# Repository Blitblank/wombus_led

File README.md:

# WombusLED

Firmware for controlling WS2812b matrices with ESP-IDF.
This embedded application is designed around the hardware described in this repository, though the goal is to broaden to other hardware targets.
The primary target is the ESP32-S3 Wroom1 N4R2 module.
KiCad schematic and PCB layout files can be found in the pcb directory.

Scripts are in scripts directory, named appropriately.

## Development plan: 
- [x] Create repository.
- [x] Build setup, get working hello-world program.
- [x] Develop 7-segment display driver for the soburg-v2 board, which uses 32-bit shift registers.
    Ensures functional hardware interaction and interface design.
- [x] Develop WS2812b driver, would be nice to have some kind of testing for this.
- [x] Develop WS2812b interface. I like the FastLed library for Arduino so might have a lot of similar functionality.
- [ ] Implement proper app structure, with error checking and performance profiling
- [ ] Add a couple LED effects- the random blink and rainbow sweep are easy ones.
- [ ] Create a mock LED panel that executes natively to test LED effects outside of hardware. (SDL2 or something)
      Should use the same interface but a different driver (that's probably integrated into the program)
      Needs to be updated to support the same control interfaces implemented on hardware.
- [ ] Add support for the aforementioned hardware control interfaces.
      (Dedicated control board may vary, main one not even designed yet)
      Buttons for switching effects, potentiometers, rotary encoders, 7 segement displays, OLED panel, etc.
- [ ] Checkpoint at a Conway's Game of Life effect that can be modified by controls (speed, brightness, reset)
- [ ] Design this far out is murky, anything past this point is a future ambition
- [ ] MicroSD card for bitmap effects. Implies custom images and animations, config for which can be in a yaml or something
- [ ] Microphone for sound-based effects like a spectrum analyzer
    
This is basic but hopefully can be good platform for future WS2812b projects.

## Scripts:
After cloning: $ ./scripts/repo-setup # installs esp-idf, sets up target configurations\
To build:      $ ./scripts/build.sh\
To flash:      $ ./scripts/flash.sh # note: flash.sh automatically builds\
To monitor:    $ ./scripts/monitor.sh\

## TODOs for developers
- [ ] Move all hardware specifications to config/Kconfig.projbuild file. (things like NUM_LEDS, pins.h, ssd_digits, etc.)
- [ ] Create an effect base class for effects to inherit from
- [ ] Attach interrupts for hardware inputs
- [ ] Human I/O (like from buttons, knobs) needs to be in its own io task. Other tasks will be injected with a general I/O interface
- [ ] Investigate putting the wsled task on a separate core from io and such
- [ ] Wsled interface needs a platform for matrix creation

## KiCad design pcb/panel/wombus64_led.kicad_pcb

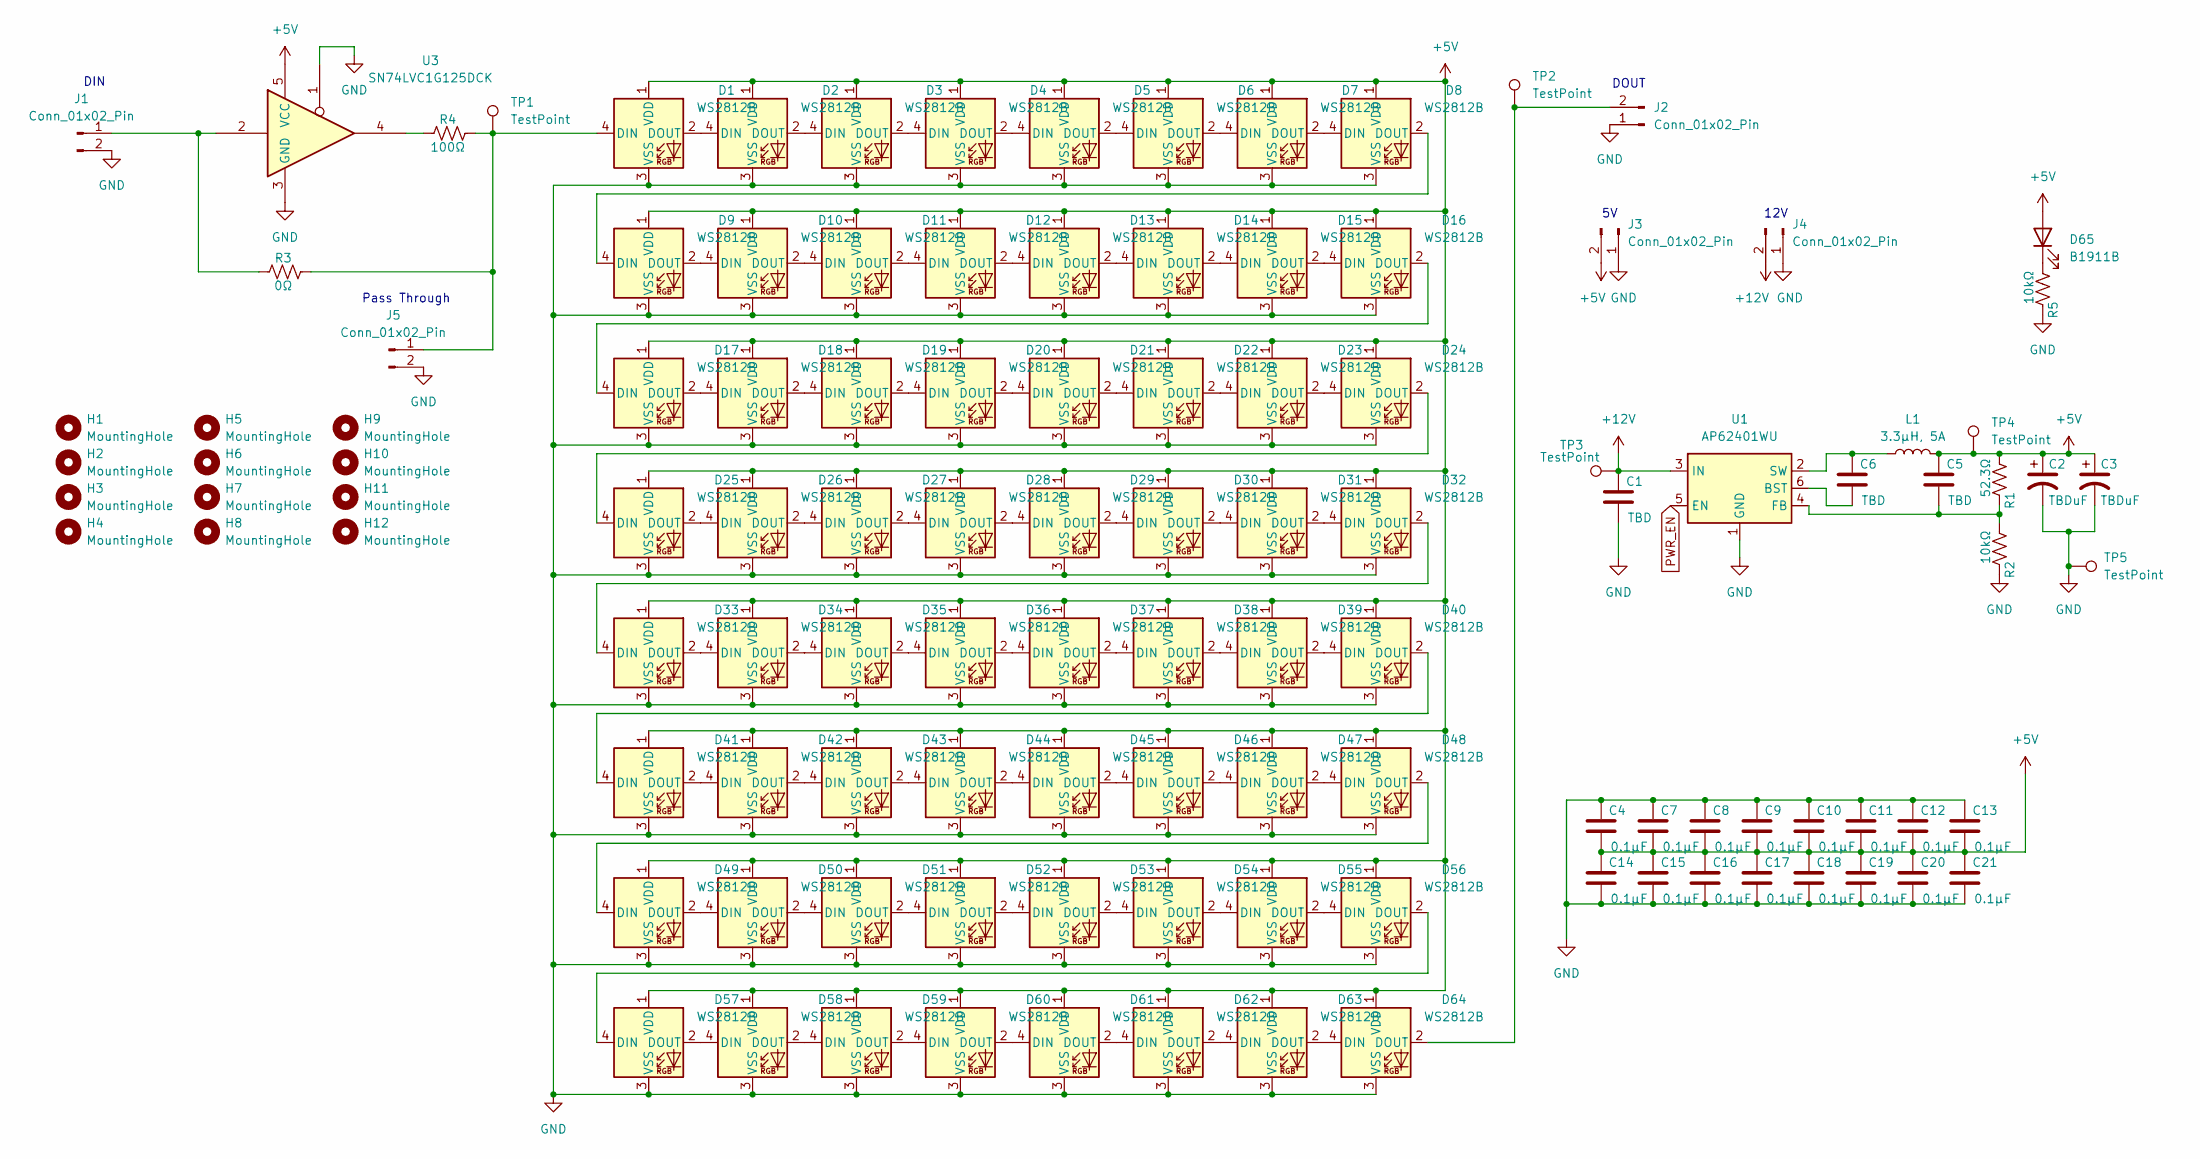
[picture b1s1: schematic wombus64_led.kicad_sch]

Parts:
C1, C5, C6: TBD; C_0603_1608Metric
C2, C3: TBDuF; CP_Radial_D8.0mm_P5.00mm
C4, C7, C8, C9, C10, C11, C12, C13, C14, C15, C16, C17, C18, C19, C20, C21: 0.1μF; C_0603_1608Metric
D1, D2, D3, D4, D5, D6, D7, D8, D9, D10, D11, D12, D13, D14, D15, D16, D17, D18, D19, D20, D21, D22, D23, D24, D25, D26, D27, D28, D29, D30, D31, D32, D33, D34, D35, D36, D37, D38, D39, D40, D41, D42, D43, D44, D45, D46, D47, D48, D49, D50, D51, D52, D53, D54, D55, D56, D57, D58, D59, D60, D61, D62, D63, D64: WS2812B; LED_WS2812B_PLCC4_5.0x5.0mm_P3.2mm
D65: B1911B; D_0603_1608Metric
H1, H2, H3, H4, H5, H6, H7, H8, H9, H10, H11, H12: MountingHole; MountingHole_3.2mm_M3_Pad
J1, J2, J3, J4, J5: Conn_01x02_Pin; JST_PH_S2B-PH-K_1x02_P2.00mm_Horizontal
L1: 3.3μH, 5A; L_TDK_VLS6045EX_VLS6045AF
R1: 52.3Ω; R_0603_1608Metric
R2, R5: 10kΩ; R_0603_1608Metric
R3: 0Ω; R_0603_1608Metric
R4: 100Ω; R_0603_1608Metric
TP1, TP2, TP3, TP4, TP5: TestPoint; TestPoint_Pad_D1.0mm
U1: AP62401WU; TSOT-23-6
U3: SN74LVC1G125DCK; Texas_R-PDSO-G5_DCK-5

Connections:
+5V: C2.1, C3.1, C4.2, C5.1, C7.2, C8.2, C9.2, C10.2, C11.2, C12.2, C13.2, C14.1, C15.1, C16.1, C17.1, C18.1, C19.1, C20.1, C21.1, D1.1 (VDD), D2.1 (VDD), D3.1 (VDD), D4.1 (VDD), D5.1 (VDD), D6.1 (VDD), D7.1 (VDD), D8.1 (VDD), D9.1 (VDD), D10.1 (VDD), D11.1 (VDD), D12.1 (VDD), D13.1 (VDD), D14.1 (VDD), D15.1 (VDD), D16.1 (VDD), D17.1 (VDD), D18.1 (VDD), D19.1 (VDD), D20.1 (VDD), D21.1 (VDD), D22.1 (VDD), D23.1 (VDD), D24.1 (VDD), D25.1 (VDD), D26.1 (VDD), D27.1 (VDD), D28.1 (VDD), D29.1 (VDD), D30.1 (VDD), D31.1 (VDD), D32.1 (VDD), D33.1 (VDD), D34.1 (VDD), D35.1 (VDD), D36.1 (VDD), D37.1 (VDD), D38.1 (VDD), D39.1 (VDD), D40.1 (VDD), D41.1 (VDD), D42.1 (VDD), D43.1 (VDD), D44.1 (VDD), D45.1 (VDD), D46.1 (VDD), D47.1 (VDD), D48.1 (VDD), D49.1 (VDD), D50.1 (VDD), D51.1 (VDD), D52.1 (VDD), D53.1 (VDD), D54.1 (VDD), D55.1 (VDD), D56.1 (VDD), D57.1 (VDD), D58.1 (VDD), D59.1 (VDD), D60.1 (VDD), D61.1 (VDD), D62.1 (VDD), D63.1 (VDD), D64.1 (VDD), D65.2 (A), J3.2, L1.2, R1.1, TP4.1, U3.5 (VCC)
+12V: C1.1, J4.2, TP3.1, U1.3 (IN)
GND: C1.2, C2.2, C3.2, C4.1, C7.1, C8.1, C9.1, C10.1, C11.1, C12.1, C13.1, C14.2, C15.2, C16.2, C17.2, C18.2, C19.2, C20.2, C21.2, D1.3 (VSS), D2.3 (VSS), D3.3 (VSS), D4.3 (VSS), D5.3 (VSS), D6.3 (VSS), D7.3 (VSS), D8.3 (VSS), D9.3 (VSS), D10.3 (VSS), D11.3 (VSS), D12.3 (VSS), D13.3 (VSS), D14.3 (VSS), D15.3 (VSS), D16.3 (VSS), D17.3 (VSS), D18.3 (VSS), D19.3 (VSS), D20.3 (VSS), D21.3 (VSS), D22.3 (VSS), D23.3 (VSS), D24.3 (VSS), D25.3 (VSS), D26.3 (VSS), D27.3 (VSS), D28.3 (VSS), D29.3 (VSS), D30.3 (VSS), D31.3 (VSS), D32.3 (VSS), D33.3 (VSS), D34.3 (VSS), D35.3 (VSS), D36.3 (VSS), D37.3 (VSS), D38.3 (VSS), D39.3 (VSS), D40.3 (VSS), D41.3 (VSS), D42.3 (VSS), D43.3 (VSS), D44.3 (VSS), D45.3 (VSS), D46.3 (VSS), D47.3 (VSS), D48.3 (VSS), D49.3 (VSS), D50.3 (VSS), D51.3 (VSS), D52.3 (VSS), D53.3 (VSS), D54.3 (VSS), D55.3 (VSS), D56.3 (VSS), D57.3 (VSS), D58.3 (VSS), D59.3 (VSS), D60.3 (VSS), D61.3 (VSS), D62.3 (VSS), D63.3 (VSS), D64.3 (VSS), J1.2, J2.1, J3.1, J4.1, J5.2, R2.2, R5.2, TP5.1, U1.1 (GND), U3.1, U3.3 (GND)
unnamed: D1.4 (DIN), J5.1, R3.2, R4.2, TP1.1
unnamed: D1.2 (DOUT), D2.4 (DIN)
unnamed: D2.2 (DOUT), D3.4 (DIN)
unnamed: D3.2 (DOUT), D4.4 (DIN)
unnamed: D4.2 (DOUT), D5.4 (DIN)
unnamed: D5.2 (DOUT), D6.4 (DIN)
unnamed: D6.2 (DOUT), D7.4 (DIN)
unnamed: D7.2 (DOUT), D8.4 (DIN)
unnamed: D8.2 (DOUT), D9.4 (DIN)
unnamed: D9.2 (DOUT), D10.4 (DIN)
unnamed: D10.2 (DOUT), D11.4 (DIN)
unnamed: D11.2 (DOUT), D12.4 (DIN)
unnamed: D12.2 (DOUT), D13.4 (DIN)
unnamed: D13.2 (DOUT), D14.4 (DIN)
unnamed: D14.2 (DOUT), D15.4 (DIN)
unnamed: D15.2 (DOUT), D16.4 (DIN)
unnamed: D16.2 (DOUT), D17.4 (DIN)
unnamed: D17.2 (DOUT), D18.4 (DIN)
unnamed: D18.2 (DOUT), D19.4 (DIN)
unnamed: D19.2 (DOUT), D20.4 (DIN)
unnamed: D20.2 (DOUT), D21.4 (DIN)
unnamed: D21.2 (DOUT), D22.4 (DIN)
unnamed: D22.2 (DOUT), D23.4 (DIN)
unnamed: D23.2 (DOUT), D24.4 (DIN)
unnamed: D24.2 (DOUT), D25.4 (DIN)
unnamed: D25.2 (DOUT), D26.4 (DIN)
unnamed: D26.2 (DOUT), D27.4 (DIN)
unnamed: D27.2 (DOUT), D28.4 (DIN)
unnamed: D28.2 (DOUT), D29.4 (DIN)
unnamed: D29.2 (DOUT), D30.4 (DIN)
unnamed: D30.2 (DOUT), D31.4 (DIN)
unnamed: D31.2 (DOUT), D32.4 (DIN)
unnamed: D32.2 (DOUT), D33.4 (DIN)
unnamed: D33.2 (DOUT), D34.4 (DIN)
unnamed: D34.2 (DOUT), D35.4 (DIN)
unnamed: D35.2 (DOUT), D36.4 (DIN)
unnamed: D36.2 (DOUT), D37.4 (DIN)
unnamed: D37.2 (DOUT), D38.4 (DIN)
unnamed: D38.2 (DOUT), D39.4 (DIN)
unnamed: D39.2 (DOUT), D40.4 (DIN)
unnamed: D40.2 (DOUT), D41.4 (DIN)
unnamed: D41.2 (DOUT), D42.4 (DIN)
unnamed: D42.2 (DOUT), D43.4 (DIN)
unnamed: D43.2 (DOUT), D44.4 (DIN)
unnamed: D44.2 (DOUT), D45.4 (DIN)
unnamed: D45.2 (DOUT), D46.4 (DIN)
unnamed: D46.2 (DOUT), D47.4 (DIN)
unnamed: D47.2 (DOUT), D48.4 (DIN)
unnamed: D48.2 (DOUT), D49.4 (DIN)
unnamed: D49.2 (DOUT), D50.4 (DIN)
unnamed: D50.2 (DOUT), D51.4 (DIN)
unnamed: D51.2 (DOUT), D52.4 (DIN)
unnamed: D52.2 (DOUT), D53.4 (DIN)
unnamed: D53.2 (DOUT), D54.4 (DIN)
unnamed: D54.2 (DOUT), D55.4 (DIN)
unnamed: D55.2 (DOUT), D56.4 (DIN)
unnamed: D56.2 (DOUT), D57.4 (DIN)
unnamed: D57.2 (DOUT), D58.4 (DIN)
unnamed: D58.2 (DOUT), D59.4 (DIN)
unnamed: D59.2 (DOUT), D60.4 (DIN)
unnamed: D60.2 (DOUT), D61.4 (DIN)
unnamed: D61.2 (DOUT), D62.4 (DIN)
unnamed: D62.2 (DOUT), D63.4 (DIN)
unnamed: D63.2 (DOUT), D64.4 (DIN)
unnamed: D64.2 (DOUT), J2.2, TP2.1
unnamed: D65.1 (K), R5.1
unnamed: J1.1, R3.1, U3.2
unnamed: R4.1, U3.4
unnamed: C6.2, U1.6 (BST)
unnamed: C5.2, R1.2, R2.1, U1.4 (FB)
unnamed: C6.1, L1.1, U1.2 (SW)
PWR_EN: U1.5 (EN)

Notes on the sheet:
Pass Through
12V
DIN
DOUT

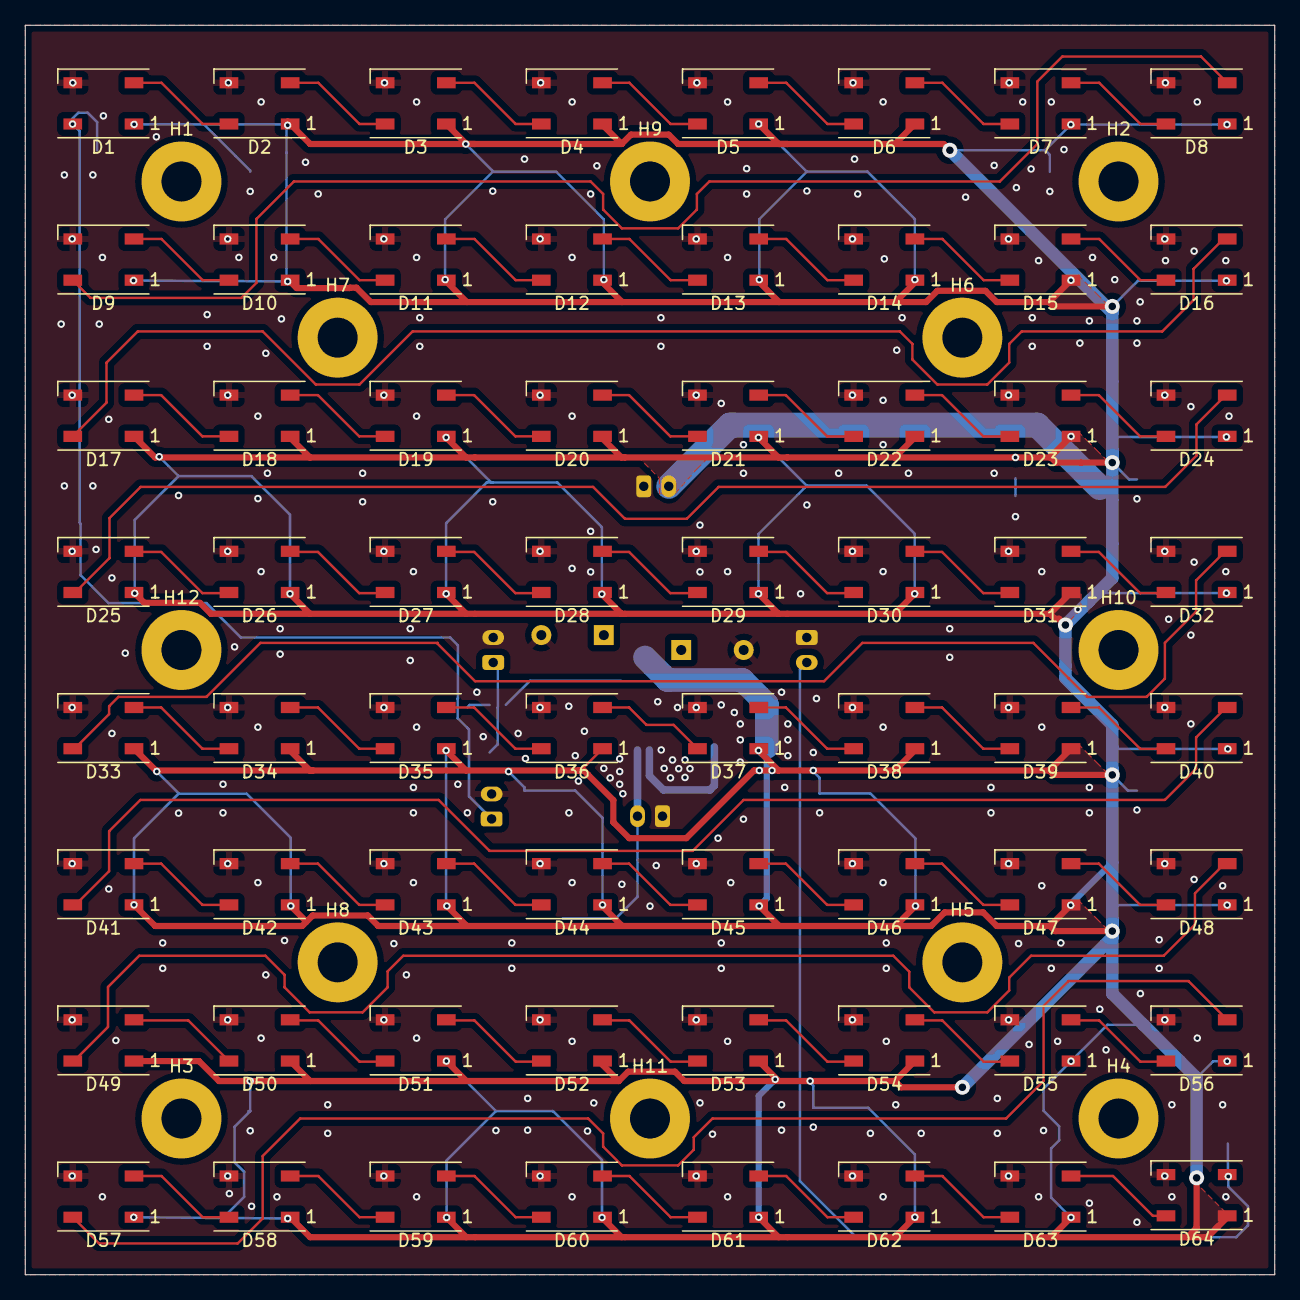
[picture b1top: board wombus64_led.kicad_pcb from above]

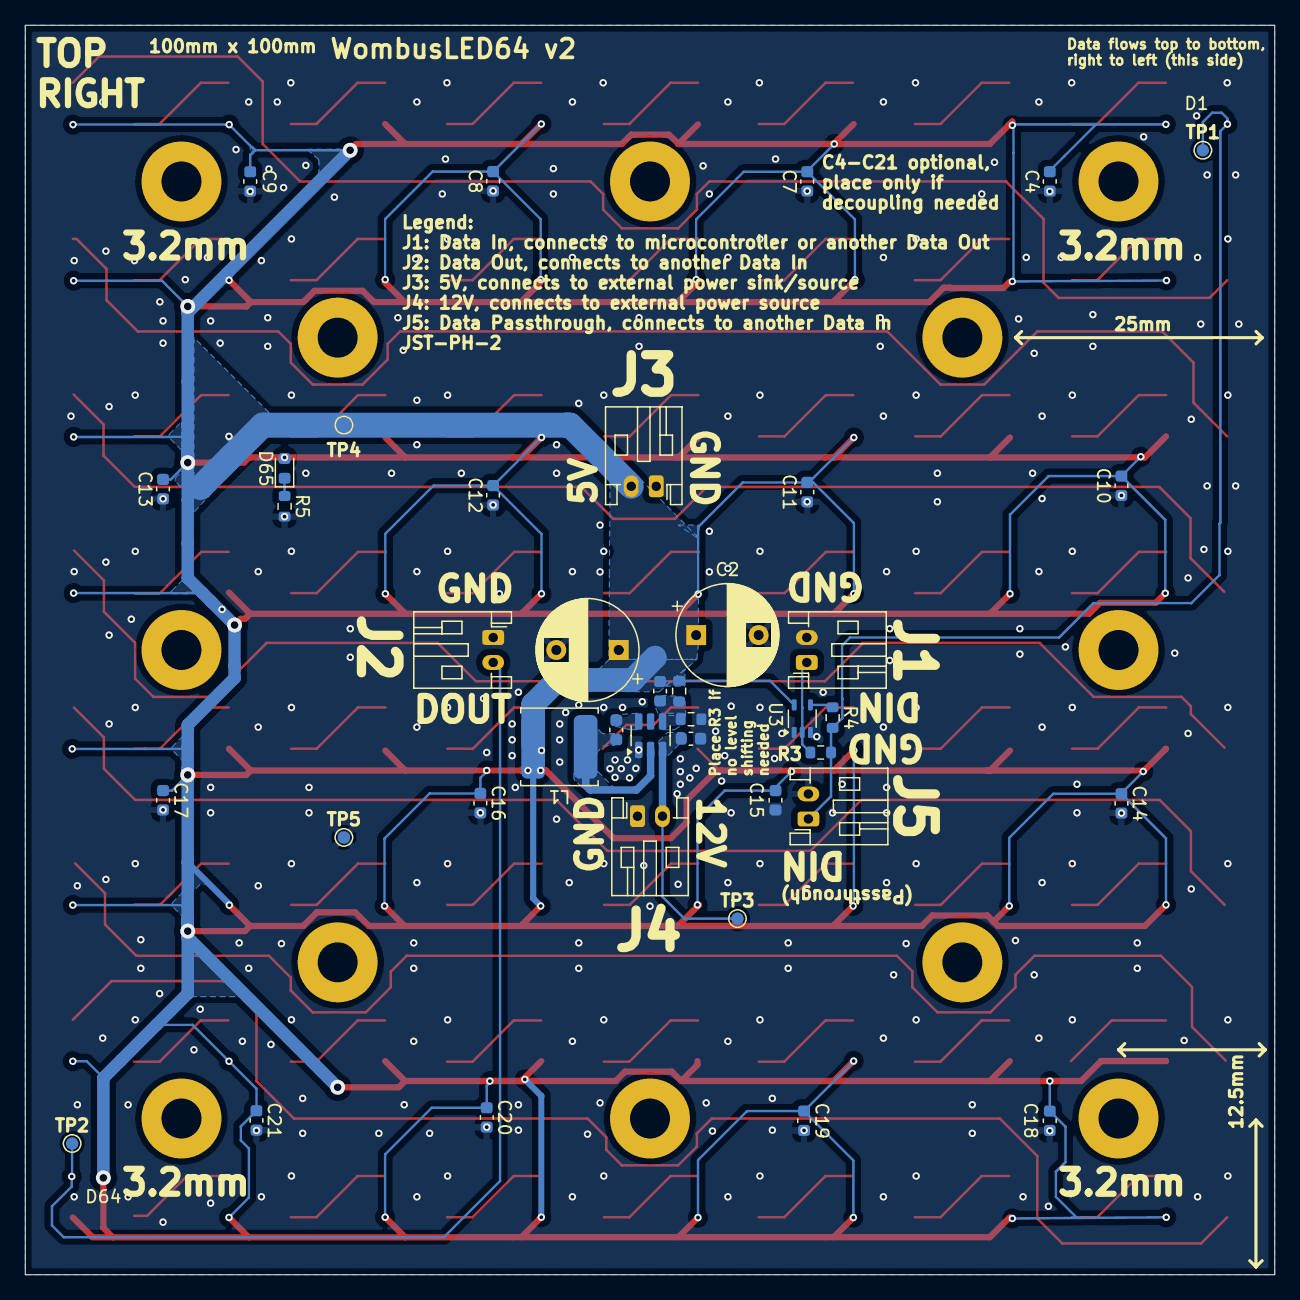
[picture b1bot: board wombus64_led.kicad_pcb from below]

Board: 2 copper layers, 100.0 x 100.0 mm, 116 parts (40 on the bottom side), 74 nets.

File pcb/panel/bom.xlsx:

| Category | Part Name | Schematic Reference | Supplier | Part # | Datasheet | Unit Price | Quantity | Shipping | Total Price | Notes |  | # Per Unit | Partial Cost |  | Notes
 | Addressable LED | WS2812B | D1-D64 | Aliexpress | - | link | 2.5000000000000001E-2 | 1000 | 0 | 25 |  |  | 64 | 1.6
 | Buck Converter | AP62401WU | U1 | Digikey | 31-AP62401WU-7CT-ND | link | 0.22789999999999999 | 100 | 0 | 22.79 |  |  | 1 | 0.22789999999999999
 | Inductor | 3.3μH, 5A | L1 | Digikey | 445-173052-1-ND | link | 0.23330000000000001 | 100 | 0 | 23.330000000000002 |  |  | 1 | 0.23330000000000001
 | WTB Connector | JST PH-2 Horizontal | J1-J5 | Digikey | 455-1719-ND | link | 6.9800000000000001E-2 | 100 | 0 | 6.98 |  |  | 5 | 0.34899999999999998
 | Level Shifter | SN74LVC1G125DCK | U3 | Digikey | 296-11604-1-ND | link | 0.06 | 50 | 0 | 3 |  |  | 0 | 0
 | Indicator LED (Red) | B1911R | D65 | Digikey | LED RED DIFFUSED 0603 SMD | link | 4.2999999999999997E-2 | 50 | 0 | 2.15 |  |  | 1 | 4.2999999999999997E-2
 |  |  |  |  |  |  |  |  | 0 | 0 |  |  |  | 0
 | Resistor | 52.3kΩ 1%, 0603 | R1 | Digikey | 311-52.3KHRCT-ND | link | 1.06E-2 | 100 | 0 | 1.06 |  |  | 1 | 1.06E-2
 | Resistor | 10kΩ 1%, 0603 | R2, R5 | Digikey | already have lots |  | 0.01 | 0 | 0 | 0 |  |  | 2 | 0.02
 | Resistor | 0Ω, 0603 | R3 | Digikey | already have lots |  | 0.01 | 0 | 0 | 0 |  |  | 1 | 0.01
 | Resistor | 100Ω 1%, 0603 | R4 | Digikey | CR0603-FX-1000ELFCT-ND | link | 9.1000000000000004E-3 | 100 | 0 | 0.91 |  |  | 1 | 9.1000000000000004E-3
 |  |  |  |  |  |  |  |  | 0 | 0 |  |  |  | 0
 | Capacitor, Ceramic | 10μF 6.3V, 0603 | C1 | Digikey | already have lots |  | 8.0000000000000002E-3 | 0 | 0 | 0 |  |  | 1 | 8.0000000000000002E-3
 | Capacitor, Electrolytic | 100μF 25V | C2, C3 | Aliexpress | - |  | 2.7400000000000001E-2 | 50 | 0 | 1.37 |  |  | 2 | 5.4800000000000001E-2
 | Capacitor, Ceramic | 0.1μF 25V, 0603 | C4, C6-C21 | Digikey | already have lots |  | 8.0000000000000002E-3 | 0 | 0 | 0 |  |  | 1 | 8.0000000000000002E-3
 | Capacitor, Ceramic | 20pF 50pF, 0603 | C5 | Digikey | already have lots |  | 8.0000000000000002E-3 | 0 | 0 | 0 |  |  | 1 | 8.0000000000000002E-3
 |  |  |  |  |  |  |  |  | 0 | 0 |  |  |  | 0
 |  |  |  |  |  |  |  |  | 0 | 0 |  |  |  | 0
 |  |  |  |  |  |  |  |  | 0 | 0 |  |  |  | 0
 |  |  |  |  |  |  |  |  | 0 | 0 |  |  |  | 0
 |  |  |  |  |  |  |  |  | 0 | 0 |  |  |  | 0
 |  |  |  |  |  |  |  |  | 0 | 0 |  |  |  | 0
 |  |  |  |  |  |  |  |  | 0 | 0 |  |  |  | 0
 |  |  |  |  |  |  |  |  | 0 | 0 |  |  |  | 0
 |  |  |  |  |  |  |  |  | 0 | 0 |  |  |  | 0
 |  |  |  |  |  |  |  |  | 0 | 0 |  |  |  | 0
 |  |  |  |  |  |  |  |  | 0 | 0 |  |  |  | 0
 |  |  |  |  |  |  |  |  | 0 | 0 |  |  |  | 0
 |  |  |  |  |  |  |  |  | 0 | 0 |  |  |  | 0
 |  |  |  |  |  |  |  |  | 0 | 0 |  |  |  | 0
 |  |  |  |  |  |  |  |  | 0 | 0 |  |  |  | 0
 |  |  |  |  |  |  |  |  | 0 | 0 |  |  |  | 0
 |  |  |  |  |  |  |  |  | 0 | 0 |  |  |  | 0
 |  |  |  |  |  |  |  |  | 0 | 0 |  |  |  | 0
 |  |  |  |  |  |  |  |  | 0 | 0 |  |  |  | 0
 |  |  |  |  |  |  |  |  | 0 | 0 |  |  |  | 0
 |  |  |  |  |  |  |  |  | 0 | 0 |  |  |  | 0
 |  |  |  |  |  |  |  |  | 0 | 0 |  |  |  | 0
 |  |  |  |  |  |  |  |  | 0 | 0 |  |  |  | 0
 |  |  |  |  |  |  |  |  | 0 | 0 |  |  |  | 0
 |  |  |  |  |  |  |  |  | 0 | 0 |  |  |  | 0
 |  |  |  |  |  |  |  |  | 0 | 0 |  |  |  | 0
 |  |  |  |  |  |  |  |  | 0 | 0 |  |  |  | 0
 |  |  |  |  |  |  |  |  | 0 | 0 |  |  |  | 0
 |  |  |  |  |  |  |  |  | 0 | 0 |  |  |  | 0
 |  |  |  |  |  |  |  |  | 0 | 0 |  |  |  | 0
 |  |  |  |  |  |  |  |  | 0 | 0 |  |  |  | 0
 |  |  |  |  |  |  |  |  | 0 | 0 |  |  |  | 0
 |  |  |  |  |  |  |  | Totals: | 0 | 86.590000000000018 | 86.590000000000018 |  |  | 2.5817000000000001

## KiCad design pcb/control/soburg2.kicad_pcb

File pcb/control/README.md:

the pcb in this directory is for a synthesizer with a load of extra peripherals,
which acts as a platform to base this control board off of. This is not the actual control board
but has capability to output WS2812b data from an ESP32-S3 Wroom1 module.

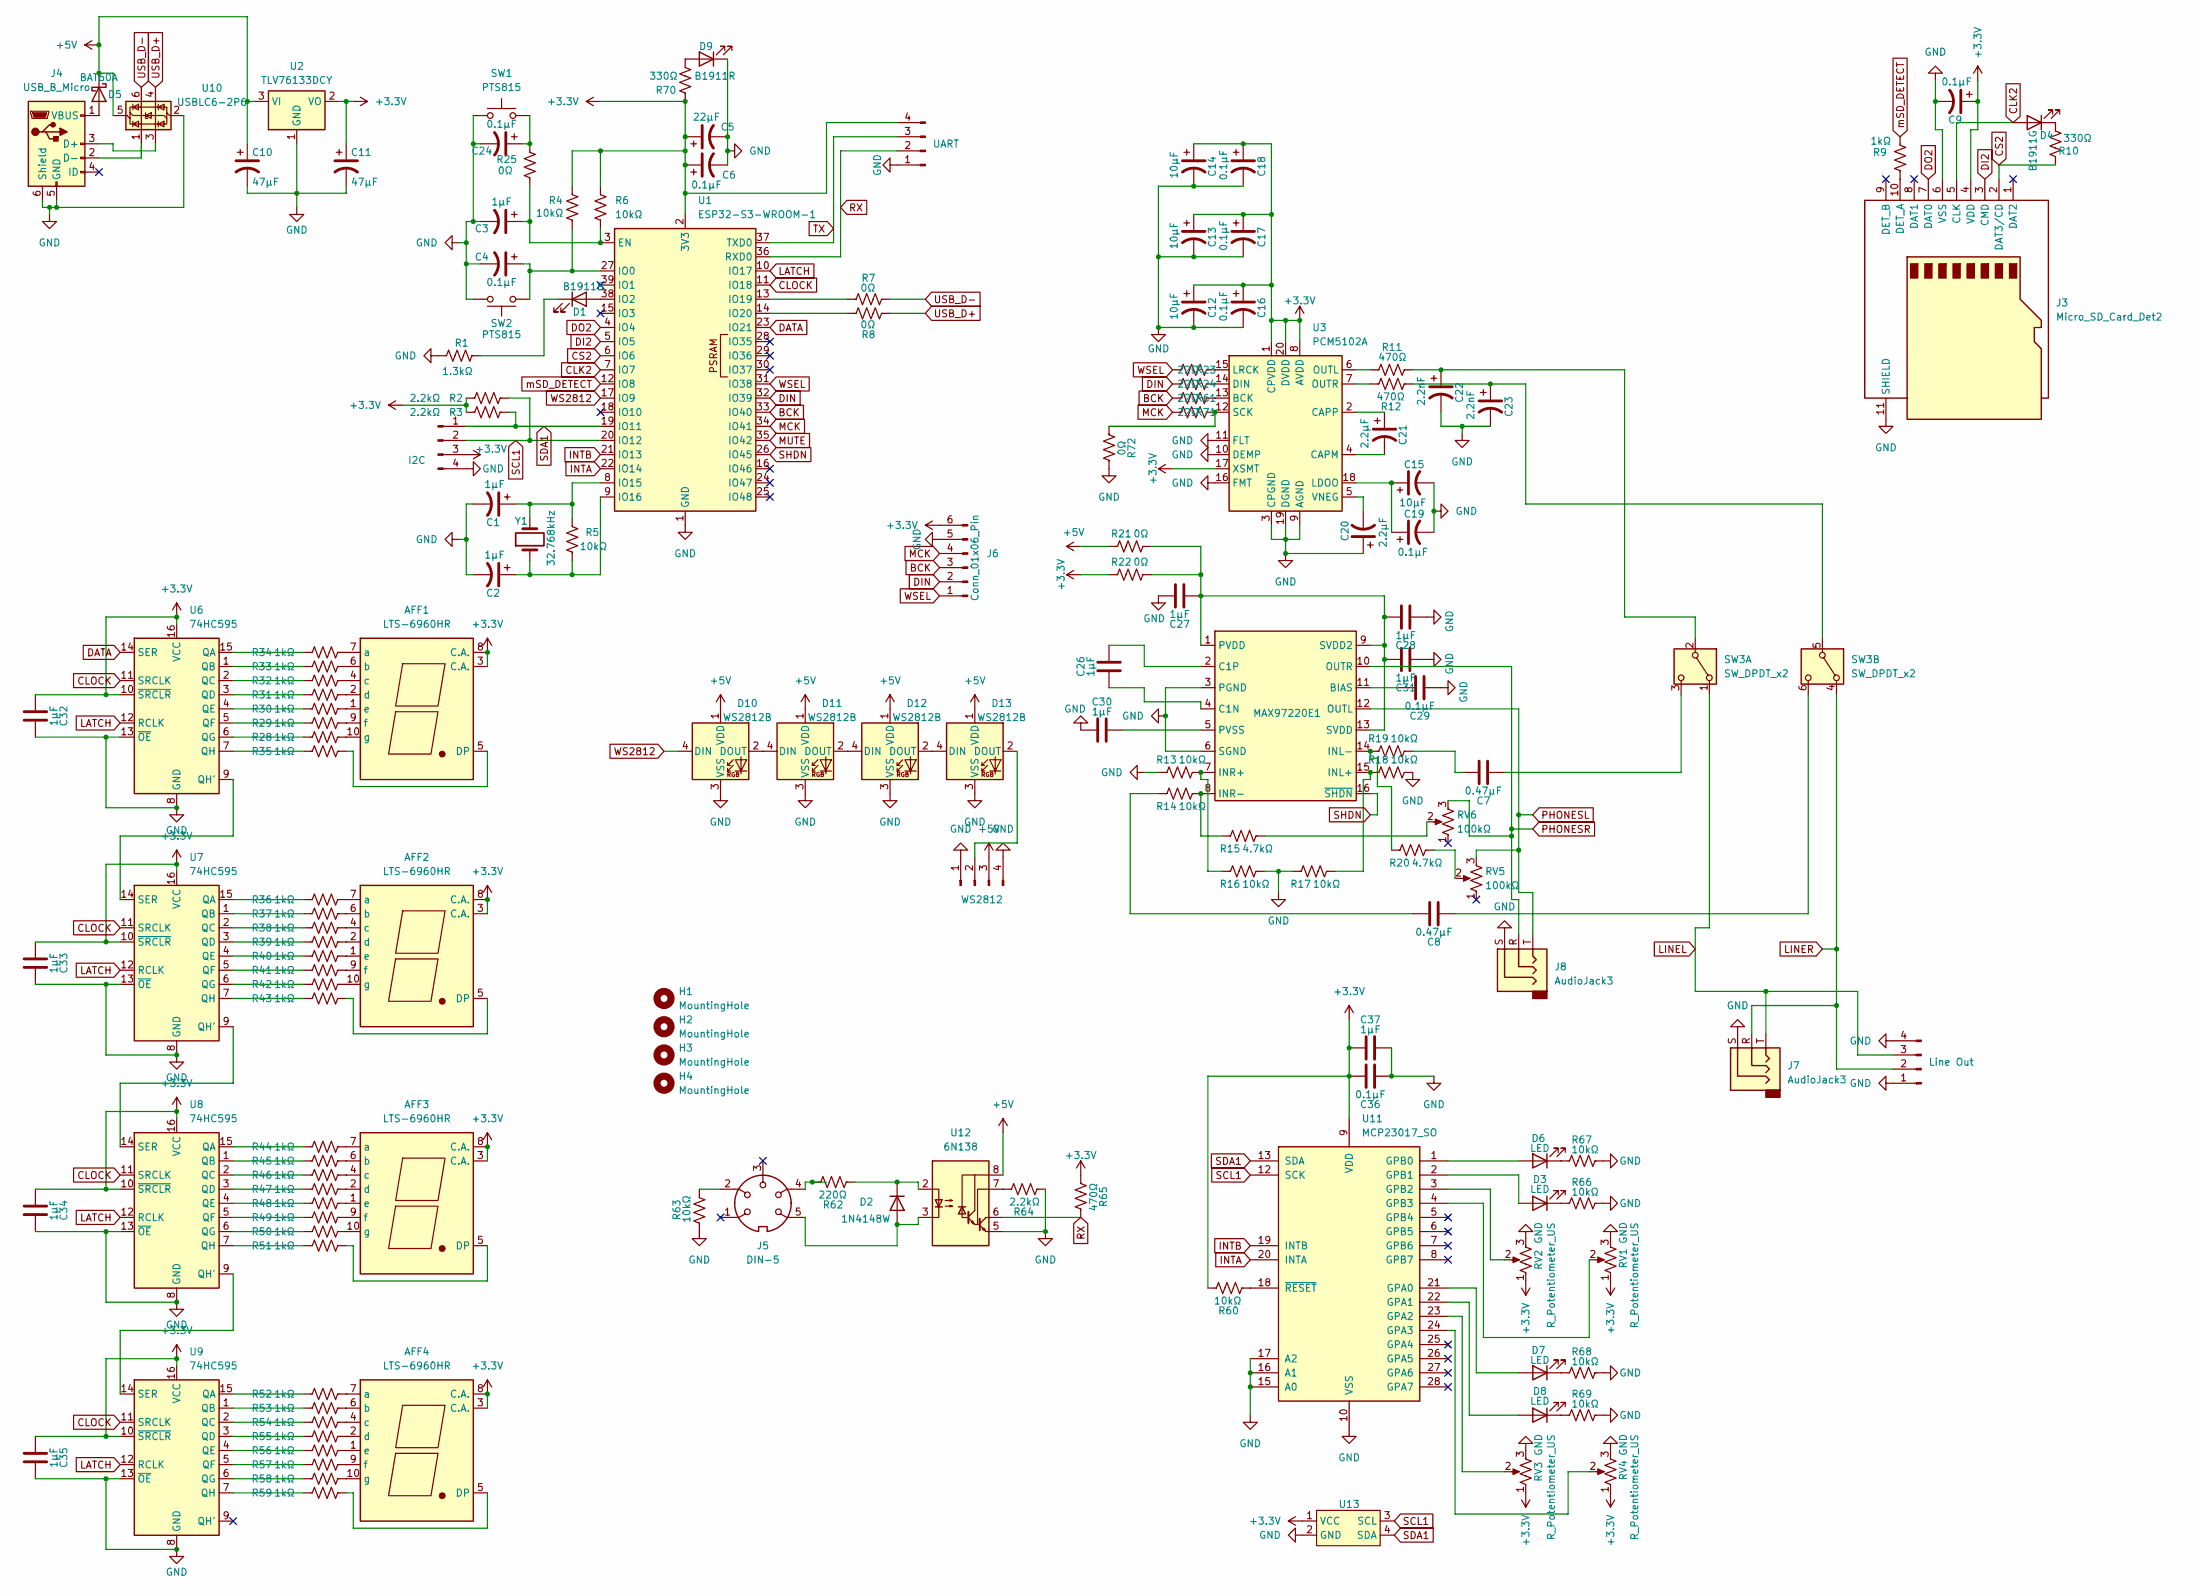
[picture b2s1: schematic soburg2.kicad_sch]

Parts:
AFF1, AFF2, AFF3, AFF4: LTS-6960HR; 7SegmentLED_LTS6760_LTS6780
C1, C2, C3, C26, C27, C28, C30, C31, C32, C33, C34, C35, C37: 1µF; C_0603_1608Metric
C4, C6, C9, C16, C17, C18, C19, C24, C29, C36: 0.1µF; C_0603_1608Metric
C5: 22µF; C_0603_1608Metric
C7, C8: 0.47µF; C_0603_1608Metric
C10, C11: 47µF; CP_Elec_5x5.4
C12, C13, C14, C15: 10µF; C_0603_1608Metric
C20, C21: 2.2µF; C_0603_1608Metric
C22, C23: 2.2nF; C_0603_1608Metric
D1: B1911B; D_0603_1608Metric
D2: 1N4148W; D_SOD-123
D3, D6, D7, D8: LED; LED_D3.0mm
D4: B1911G; D_0603_1608Metric
D5: BAT60A; D_SOD-323
D9: B1911R; D_0603_1608Metric
D10, D11, D12, D13: WS2812B; LED_WS2812B_PLCC4_5.0x5.0mm_P3.2mm
H1, H2, H3, H4: MountingHole; MountingHole_3.2mm_M3_ISO14580_Pad
J1: I2C; JST_PH_B4B-PH-K_1x04_P2.00mm_Vertical
J2: UART; JST_PH_B4B-PH-K_1x04_P2.00mm_Vertical
J3: Micro_SD_Card_Det2; microSD_HC_Molex_104031-0811
J4: USB_B_Micro; USB_Micro-B_Amphenol_10118194_Horizontal
J5: DIN-5; DIN-5_MIDI
J6: Conn_01x06_Pin; JST_PH_B6B-PH-K_1x06_P2.00mm_Vertical
J7: AudioJack3; Jack_6.35mm_Neutrik_NMJ6HFD4_Horizontal
J8: AudioJack3; 54-00178 jack
J9: Line Out; JST_PH_B4B-PH-K_1x04_P2.00mm_Vertical
J10: WS2812; JST_PH_B4B-PH-K_1x04_P2.00mm_Vertical
MAX97220E1: TQFN-16-1EP_3x3mm_P0.5mm_EP1.23x1.23mm
R1: 1.3kΩ; R_0603_1608Metric
R2, R3, R64: 2.2kΩ; R_0603_1608Metric
R4, R5, R6, R13, R14, R16, R17, R18, R19, R60, R63, R66, R67, R68, R69: 10kΩ; R_0603_1608Metric
R7, R8, R21, R22, R25, R72: 0Ω; R_0603_1608Metric
R9, R28, R29, R30, R31, R32, R33, R34, R35, R36, R37, R38, R39, R40, R41, R42, R43, R44, R45, R46, R47, R48, R49, R50, R51, R52, R53, R54, R55, R56, R57, R58, R59: 1kΩ; R_0603_1608Metric
R10, R70: 330Ω; R_0603_1608Metric
R11, R12, R65: 470Ω; R_0603_1608Metric
R15, R20: 4.7kΩ; R_0603_1608Metric
R23, R24, R61, R71: 22Ω; R_0603_1608Metric
R62: 220Ω; R_0603_1608Metric
RV1, RV2, RV3, RV4: R_Potentiometer_US; Potentiometer_Bourns_TC33X_Vertical
RV5, RV6: 100kΩ; Potentiometer_Bourns_TC33X_Vertical
SW1, SW2: PTS815
SW3: SW_DPDT_x2; slide_switch dpdt (SLW-867569-4A-N-D)
U1: ESP32-S3-WROOM-1
U2: TLV76133DCY; SOT-223-3_TabPin2
U3: PCM5102A; TSSOP-20_4.4x6.5mm_P0.65mm
U6, U7, U8, U9: 74HC595; TSSOP-16-1EP_4.4x5mm_P0.65mm_EP3x3mm
U10: USBLC6-2P6; SOT-23-6
U11: MCP23017_SO; SOIC-28W_7.5x17.9mm_P1.27mm
U12: 6N138; DIP-8_W8.89mm_SMDSocket_LongPads
U13: oled-i2c-module
Y1: 32.768kHz; Crystal_SMD_3225-4Pin_3.2x2.5mm

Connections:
+3.3V: AFF1.3 (C.A.), AFF1.8 (C.A.), AFF2.3 (C.A.), AFF2.8 (C.A.), AFF3.3 (C.A.), AFF3.8 (C.A.), AFF4.3 (C.A.), AFF4.8 (C.A.), C5.1, C6.1, C9.1, C11.1, C12.1, C13.1, C14.1, C16.1, C17.1, C18.1, C32.1, C33.1, C34.1, C35.1, C36.2, C37.1, J1.3, J2.4, J3.4 (VDD), J6.6, R2.1, R3.1, R4.1, R6.1, R22.2, R60.2, R65.1, R70.1, RV1.1, RV2.1, RV3.1, RV4.1, U1.2 (3V3), U2.2 (VO), U3.1 (CPVDD), U3.8 (AVDD), U3.17 (XSMT), U3.20 (DVDD), U6.10 (~SRCLR), U6.16 (VCC), U7.10 (~SRCLR), U7.16 (VCC), U8.10 (~SRCLR), U8.16 (VCC), U9.10 (~SRCLR), U9.16 (VCC), U11.9 (VDD), U13.1 (VCC)
+5V: C10.1, D5.1 (K), D10.1 (VDD), D11.1 (VDD), D12.1 (VDD), D13.1 (VDD), J10.3, R21.2, U2.3 (VI), U10.5 (VBUS), U12.8 (VCC)
BCK: J6.3, R61.2, U1.33 (IO40)
CLK2: D4.2 (A), J3.5 (CLK), U1.7 (IO7)
CLOCK: U1.11 (IO18), U6.11 (SRCLK), U7.11 (SRCLK), U8.11 (SRCLK), U9.11 (SRCLK)
CS2: J3.2 (DAT3/CD), R10.1, U1.6 (IO6)
DATA: U1.23 (IO21), U6.14 (SER)
DI2: J3.3 (CMD), U1.5 (IO5)
DIN: J6.2, R24.2, U1.32 (IO39)
DO2: J3.7 (DAT0), U1.4 (IO4)
GND: C1.2, C2.2, C3.2, C4.2, C5.2, C6.2, C9.2, C10.2, C11.2, C12.2, C13.2, C14.2, C15.2, C16.2, C17.2, C18.2, C19.2, C20.1, C22.2, C23.2, C24.2, C27.2, C28.1, C29.1, C30.1, C31.1, C32.2, C33.2, C34.2, C35.2, C36.1, C37.2, D9.1 (K), D10.3 (VSS), D11.3 (VSS), D12.3 (VSS), D13.3 (VSS), J1.4, J2.1, J3.6 (VSS), J3.11 (SHIELD), J4.5 (GND), J4.6 (Shield), J6.5, J7.S, J8.S, J9.1, J9.4, J10.1, J10.4, MAX97220E1.3 (PGND), MAX97220E1.6 (SGND), MAX97220E1.17, R1.1, R13.2, R16.1, R17.2, R18.1, R63.1, R64.1, R66.1, R67.1, R68.1, R69.1, R72.2, RV1.3, RV2.3, RV3.3, RV4.3, SW1.1, SW2.2, U1.1 (GND), U1.40 (GND), U1.41 (GND), U2.1 (GND), U3.3 (CPGND), U3.9 (AGND), U3.10 (DEMP), U3.11 (FLT), U3.16 (FMT), U3.19 (DGND), U6.8 (GND), U6.13 (~OE), U7.8 (GND), U7.13 (~OE), U8.8 (GND), U8.13 (~OE), U9.8 (GND), U9.13 (~OE), U10.2 (GND), U11.10 (VSS), U11.15 (A0), U11.16 (A1), U11.17 (A2), U12.5 (GND), U13.2 (GND)
INTA: U1.22 (IO14), U11.20 (INTA)
INTB: U1.21 (IO13), U11.19 (INTB)
LATCH: U1.10 (IO17), U6.12 (RCLK), U7.12 (RCLK), U8.12 (RCLK), U9.12 (RCLK)
LINEL: J7.T, J9.3, SW3.1 (A)
LINER: J7.R, J9.2, SW3.4 (A)
MCK: J6.4, R71.2, U1.34 (IO41)
MUTE: U1.35 (IO42)
unnamed: AFF1.5 (DP), R35.2
unnamed: AFF1.7 (a), R34.2
unnamed: AFF1.6 (b), R33.2
unnamed: AFF1.4 (c), R32.2
unnamed: AFF1.2 (d), R31.2
unnamed: AFF1.1 (e), R30.2
unnamed: AFF1.9 (f), R29.2
unnamed: AFF1.10 (g), R28.2
unnamed: AFF2.5 (DP), R43.2
unnamed: AFF2.7 (a), R36.2
unnamed: AFF2.6 (b), R37.2
unnamed: AFF2.4 (c), R38.2
unnamed: AFF2.2 (d), R39.2
unnamed: AFF2.1 (e), R40.2
unnamed: AFF2.9 (f), R41.2
unnamed: AFF2.10 (g), R42.2
unnamed: AFF3.5 (DP), R51.2
unnamed: AFF3.7 (a), R44.2
unnamed: AFF3.6 (b), R45.2
unnamed: AFF3.4 (c), R46.2
unnamed: AFF3.2 (d), R47.2
unnamed: AFF3.1 (e), R48.2
unnamed: AFF3.9 (f), R49.2
unnamed: AFF3.10 (g), R50.2
unnamed: AFF4.5 (DP), R59.2
unnamed: AFF4.7 (a), R52.2
unnamed: AFF4.6 (b), R53.2
unnamed: AFF4.4 (c), R54.2
unnamed: AFF4.2 (d), R55.2
unnamed: AFF4.1 (e), R56.2
unnamed: AFF4.9 (f), R57.2
unnamed: AFF4.10 (g), R58.2
unnamed: C7.2, R19.1
unnamed: C8.2, R14.2
unnamed: C24.1, R25.1, SW1.2
unnamed: D1.2 (A), U1.38 (IO2)
unnamed: D1.1 (K), R1.2
unnamed: D2.2 (A), J5.5, U12.3 (C2)
unnamed: D2.1 (K), R62.1, U12.2 (C1)
unnamed: D3.2 (A), U11.2 (GPB1)
unnamed: D3.1 (K), R66.2
unnamed: D4.1 (K), R10.2
unnamed: D5.2 (A), J4.1 (VBUS)
unnamed: D6.2 (A), U11.1 (GPB0)
unnamed: D6.1 (K), R67.2
unnamed: D7.2 (A), U11.21 (GPA0)
unnamed: D7.1 (K), R68.2
unnamed: D8.2 (A), U11.22 (GPA1)
unnamed: D8.1 (K), R69.2
unnamed: D9.2 (A), R70.2
unnamed: D10.2 (DOUT), D11.4 (DIN)
unnamed: D11.2 (DOUT), D12.4 (DIN)
unnamed: D12.2 (DOUT), D13.4 (DIN)
unnamed: D13.2 (DOUT), J10.2
unnamed: J3.10 (DET_A), R9.1
unnamed: J4.3 (D+), U10.3 (I/O2)
unnamed: J4.2 (D-), U10.1 (I/O1)
unnamed: J5.2, R63.2
unnamed: J5.4, R62.2
unnamed: C29.2, MAX97220E1.11 (BIAS)
unnamed: C26.1, MAX97220E1.4 (C1N)
unnamed: C26.2, MAX97220E1.2 (C1P)
unnamed: MAX97220E1.15 (INL+), R17.1, R18.2
unnamed: MAX97220E1.14 (INL-), R19.2, R20.2
unnamed: MAX97220E1.7 (INR+), R13.1, R16.2
unnamed: MAX97220E1.8 (INR-), R14.1, R15.2
unnamed: C27.1, C28.2, C31.2, MAX97220E1.1 (PVDD), MAX97220E1.9 (SVDD2), MAX97220E1.13 (SVDD), R21.1, R22.1
unnamed: C30.2, MAX97220E1.5 (PVSS)
unnamed: R15.1, RV6.2
unnamed: R20.1, RV5.2
unnamed: C22.1, R11.2, SW3.2 (B)
unnamed: C7.1, SW3.3 (C)
unnamed: C23.1, R12.1, SW3.5 (B)
unnamed: C8.1, SW3.6 (C)
unnamed: C3.1, R6.2, R25.2, U1.3 (EN)
unnamed: C4.1, R4.2, SW2.1, U1.27 (IO0)
unnamed: C1.1, R5.1, U1.8 (IO15), Y1.2
unnamed: C2.1, R5.2, U1.9 (IO16), Y1.1
unnamed: R7.1, U1.13 (IO19)
unnamed: R8.1, U1.14 (IO20)
unnamed: R61.1, U3.13 (BCK)
unnamed: C21.2, U3.4 (CAPM)
unnamed: C21.1, U3.2 (CAPP)
unnamed: R24.1, U3.14 (DIN)
unnamed: C15.1, C19.1, U3.18 (LDOO)
unnamed: R23.1, U3.15 (LRCK)
unnamed: R11.1, U3.6 (OUTL)
unnamed: R12.2, U3.7 (OUTR)
unnamed: R71.1, R72.1, U3.12 (SCK)
unnamed: C20.2, U3.5 (VNEG)
unnamed: R34.1, U6.15 (QA)
unnamed: R33.1, U6.1 (QB)
unnamed: R32.1, U6.2 (QC)
unnamed: R31.1, U6.3 (QD)
unnamed: R30.1, U6.4 (QE)
unnamed: R29.1, U6.5 (QF)
unnamed: R28.1, U6.6 (QG)
unnamed: U6.9 (QH'), U7.14 (SER)
unnamed: R35.1, U6.7 (QH)
unnamed: R36.1, U7.15 (QA)
unnamed: R37.1, U7.1 (QB)
unnamed: R38.1, U7.2 (QC)
unnamed: R39.1, U7.3 (QD)
unnamed: R40.1, U7.4 (QE)
unnamed: R41.1, U7.5 (QF)
unnamed: R42.1, U7.6 (QG)
unnamed: U7.9 (QH'), U8.14 (SER)
unnamed: R43.1, U7.7 (QH)
unnamed: R44.1, U8.15 (QA)
unnamed: R45.1, U8.1 (QB)
unnamed: R46.1, U8.2 (QC)
unnamed: R47.1, U8.3 (QD)
unnamed: R48.1, U8.4 (QE)
unnamed: R49.1, U8.5 (QF)
unnamed: R50.1, U8.6 (QG)
unnamed: U8.9 (QH'), U9.14 (SER)
unnamed: R51.1, U8.7 (QH)
unnamed: R52.1, U9.15 (QA)
unnamed: R53.1, U9.1 (QB)
unnamed: R54.1, U9.2 (QC)
unnamed: R55.1, U9.3 (QD)
unnamed: R56.1, U9.4 (QE)
unnamed: R57.1, U9.5 (QF)
unnamed: R58.1, U9.6 (QG)
unnamed: R59.1, U9.7 (QH)
unnamed: RV3.2, U11.23 (GPA2)
unnamed: RV4.2, U11.24 (GPA3)
unnamed: RV2.2, U11.3 (GPB2)
unnamed: RV1.2, U11.4 (GPB3)
unnamed: R60.1, U11.18 (~RESET)
unnamed: R64.2, U12.7 (VO1)
PHONESL: J8.T, MAX97220E1.12 (OUTL), RV5.3
PHONESR: J8.R, MAX97220E1.10 (OUTR), RV6.3
RX: J2.2, R65.2, U1.36 (RXD0), U12.6 (VO2)
SCL1: J1.2, R2.2, U1.20 (IO12), U11.12 (SCK), U13.3 (SCL)
SDA1: J1.1, R3.2, U1.19 (IO11), U11.13 (SDA), U13.4 (SDA)
SHDN: MAX97220E1.16 (~SHDN), U1.26 (IO45)
TX: J2.3, U1.37 (TXD0)
USB_D+: R8.2, U10.4 (I/O2)
USB_D-: R7.2, U10.6 (I/O1)
WS2812: D10.4 (DIN), U1.17 (IO9)
WSEL: J6.1, R23.2, U1.31 (IO38)
mSD_DETECT: R9.2, U1.12 (IO8)

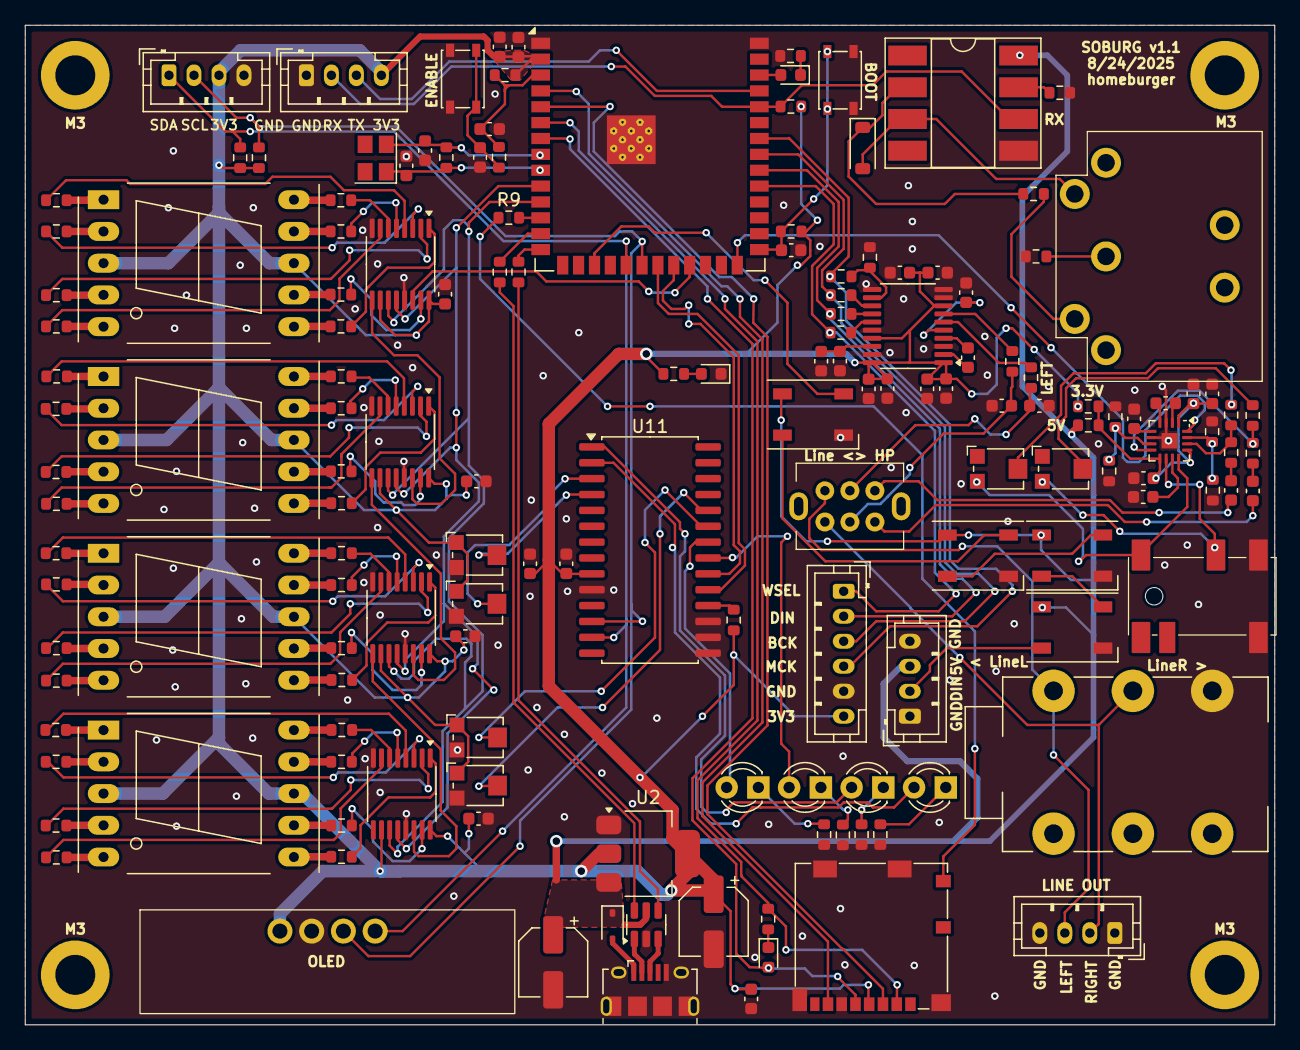
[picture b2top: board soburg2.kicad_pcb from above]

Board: 2 copper layers, 100.0 x 80.0 mm, 159 parts (0 on the bottom side), 160 nets.

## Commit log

2025-11-30 add kicad files
2025-12-01 added bill of materials
2025-12-06 build scripts and files
2025-12-06 build working
2025-12-07 move main.c to source
2025-12-07 add needed files
2025-12-07 working blink example
2025-12-07 re: working blink example
2025-12-07 c++ support
2025-12-07 re: c++ support
2025-12-07 src refactor
2025-12-07 add app
2025-12-08 add driver
2025-12-12 checkpoint
2025-12-14 add drivers and interface and task classes
2025-12-14 task base
2025-12-15 make ssd driver work
2026-02-12 add untested wsled drivers
2026-02-12 fix wsled build
2026-02-13 working wsled driver checkpoint
2026-02-13 wsled interface skeleton
2026-02-14 flesh out wsled interface
2026-02-15 reorganize project structure
2026-02-15 simplify driver to be stateless
2026-02-15 comments and update readme
